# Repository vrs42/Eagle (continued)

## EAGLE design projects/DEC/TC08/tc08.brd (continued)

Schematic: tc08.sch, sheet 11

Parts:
B02, B03, B04, B05: M623; H807
C02, C03: M101; H807

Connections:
76+77: C03.C1 (ENABLE); also elsewhere on the board
!0_TO_AC: B05.H1 (B); also elsewhere on the board
!B-BRK: B02.C1 (C), B02.F2 (C), B02.J1 (C), B02.M2 (C), B02.P1 (C), B02.T2 (C); also elsewhere on the board
!BAC_00: C03.B1 (O1); also elsewhere on the board
!BAC_01: C03.E1 (O2); also elsewhere on the board
!BAC_02: C03.H1 (O3); also elsewhere on the board
!BAC_03: C03.K1 (O4); also elsewhere on the board
!BAC_04: C03.M1 (O5); also elsewhere on the board
!BAC_05: C03.P1 (O6); also elsewhere on the board
!BAC_06: C03.S1 (O7); also elsewhere on the board
!BAC_07: C03.U1 (O8); also elsewhere on the board
!BAC_08: C03.F2 (O9); also elsewhere on the board
!BAC_09: C03.J2 (O10); also elsewhere on the board
!BAC_10: C03.L2 (O11); also elsewhere on the board
!BAC_11: C03.N2 (O12); also elsewhere on the board
!BMB_00: C02.B1 (O1); also elsewhere on the board
!BMB_01: C02.E1 (O2); also elsewhere on the board
!BMB_02: C02.H1 (O3); also elsewhere on the board
!BMB_03: C02.K1 (O4); also elsewhere on the board
!BMB_04: C02.M1 (O5); also elsewhere on the board
!BMB_05: C02.P1 (O6); also elsewhere on the board
!BMB_06: C02.S1 (O7); also elsewhere on the board
!BMB_07: C02.U1 (O8); also elsewhere on the board
!BMB_08: C02.F2 (O9); also elsewhere on the board
!BMB_09: C02.J2 (O10); also elsewhere on the board
!BMB_10: C02.L2 (O11); also elsewhere on the board
!BMB_11: C02.N2 (O12); also elsewhere on the board
!DB_00: B02.D1 (D); also elsewhere on the board
!DB_01: B02.E1 (E); also elsewhere on the board
!DB_02: B02.K1 (D); also elsewhere on the board
!DB_03: B02.L1 (E); also elsewhere on the board
!DB_04: B02.R1 (D); also elsewhere on the board
!DB_05: B02.S1 (E); also elsewhere on the board
!DB_06: B02.H2 (D); also elsewhere on the board
!DB_07: B02.J2 (E); also elsewhere on the board
!DB_08: B02.N2 (D); also elsewhere on the board
!DB_09: B02.P2 (E); also elsewhere on the board
!DB_10: B02.U2 (D); also elsewhere on the board
!DB_11: B02.V2 (E); also elsewhere on the board
!DF: B05.A1 (A); also elsewhere on the board
!DTB_00: B02.A1 (A); also elsewhere on the board
!DTB_01: B02.B1 (B); also elsewhere on the board
!DTB_02: B02.F1 (A); also elsewhere on the board
!DTB_03: B02.H1 (B); also elsewhere on the board
!DTB_04: B02.M1 (A); also elsewhere on the board
!DTB_05: B02.N1 (B); also elsewhere on the board
!DTB_06: B02.D2 (A); also elsewhere on the board
!DTB_07: B02.E2 (B); also elsewhere on the board
!DTB_08: B02.K2 (A); also elsewhere on the board
!DTB_09: B02.L2 (B); also elsewhere on the board
!DTB_10: B02.R2 (A); also elsewhere on the board
!DTB_11: B02.S2 (B); also elsewhere on the board
!DTF: B04.L2 (B); also elsewhere on the board
!EA_00: B05.R1 (D); also elsewhere on the board
!EA_01: B05.S1 (E); also elsewhere on the board
!EA_02: B05.H2 (D); also elsewhere on the board
!EF: B04.A1 (A); also elsewhere on the board
!END: B04.F1 (A); also elsewhere on the board
!ENI: B03.L2 (B); also elsewhere on the board
!FR_00: B03.N1 (B); also elsewhere on the board
!FR_01: B03.D2 (A), B05.E2 (B); also elsewhere on the board
!FR_02: B03.E2 (B); also elsewhere on the board
!FR_03: B03.K2 (A); also elsewhere on the board
!IM_00: B03.D1 (D), B04.D1 (D); also elsewhere on the board
!IM_01: B03.E1 (E), B04.E1 (E); also elsewhere on the board
!IM_02: B03.K1 (D), B04.K1 (D); also elsewhere on the board
!IM_03: B03.L1 (E), B04.L1 (E); also elsewhere on the board
!IM_04: B03.R1 (D), B04.R1 (D); also elsewhere on the board
!IM_05: B03.S1 (E), B04.S1 (E); also elsewhere on the board
!IM_06: B03.H2 (D), B04.H2 (D); also elsewhere on the board
!IM_07: B03.J2 (E), B04.J2 (E); also elsewhere on the board
!IM_08: B03.N2 (D), B04.N2 (D); also elsewhere on the board
!IM_09: B03.P2 (E); also elsewhere on the board
!IM_11: B04.P2 (E); also elsewhere on the board
!INT_RQ: B05.B1 (B); also elsewhere on the board
!MF00: B04.D2 (A), B05.M1 (A); also elsewhere on the board
!MF01: B04.E2 (B), B05.N1 (B); also elsewhere on the board
!MF02: B04.K2 (A), B05.D2 (A); also elsewhere on the board
!MKTK: B04.B1 (B); also elsewhere on the board
!MR00: B03.H1 (B); also elsewhere on the board
!MR01: B03.M1 (A); also elsewhere on the board
!PAR: B04.M1 (A); also elsewhere on the board
!RSTA: B03.C1 (C), B03.F2 (C), B03.J1 (C), B03.M2 (C), B03.P1 (C); also elsewhere on the board
!RSTB: B04.C1 (C), B04.F2 (C), B04.J1 (C), B04.M2 (C), B04.P1 (C); also elsewhere on the board
!SEARCH: B05.K2 (A); also elsewhere on the board
!SEL: B04.H1 (B); also elsewhere on the board
!SKP_RQ: B05.F1 (A); also elsewhere on the board
!TIM: B04.N1 (B); also elsewhere on the board
!USR_00: B03.A1 (A); also elsewhere on the board
!USR_01: B03.B1 (B); also elsewhere on the board
!USR_02: B03.F1 (A); also elsewhere on the board
+3V@C08U1: C02.C1 (ENABLE); also elsewhere on the board
ADDR_ACC: C02.V2 (O15); also elsewhere on the board
GND: B02.C2 (GND), B02.T1 (GND), B02.U1 (GND), B02.V1 (GND), B03.C2 (GND), B03.T1 (GND), B03.U1 (GND), B03.V1 (GND), B04.C2 (GND), B04.T1 (GND), B04.U1 (GND), B04.V1 (GND), B05.C1 (C), B05.C2 (GND), B05.F2 (C), B05.J1 (C), B05.M2 (C), B05.P1 (C), B05.T1 (GND), B05.U1 (GND), B05.V1 (GND), C02.C2 (GND), C02.T1 (GND), C03.C2 (GND), C03.T1 (GND); also elsewhere on the board
I/!O_0_TO_AC: B05.L1 (E); also elsewhere on the board
I/!O_1_TO_CA_INH: B05.N2 (D); also elsewhere on the board
I/!O_ADDR_ACC: C02.U2 (IN15); also elsewhere on the board
I/!O_BRK_RQ: B05.D1 (D); also elsewhere on the board
I/!O_INT_RQ: B05.E1 (E); also elsewhere on the board
I/!O_SKP_RQ: B05.K1 (D); also elsewhere on the board
I/O_BAC_00: C03.A1 (IN1); also elsewhere on the board
I/O_BAC_01: C03.D1 (IN2); also elsewhere on the board
I/O_BAC_02: C03.F1 (IN3); also elsewhere on the board
I/O_BAC_03: C03.J1 (IN4); also elsewhere on the board
I/O_BAC_04: C03.L1 (IN5); also elsewhere on the board
I/O_BAC_05: C03.N1 (IN6); also elsewhere on the board
I/O_BAC_06: C03.R1 (IN7); also elsewhere on the board
I/O_BAC_07: C03.V1 (IN8); also elsewhere on the board
I/O_BAC_08: C03.E2 (IN9); also elsewhere on the board
I/O_BAC_09: C03.H2 (IN10); also elsewhere on the board
I/O_BAC_10: C03.K2 (IN11); also elsewhere on the board
I/O_BAC_11: C03.M2 (IN12); also elsewhere on the board
I/O_BMB_00: C02.A1 (IN1); also elsewhere on the board
I/O_BMB_01: C02.D1 (IN2); also elsewhere on the board
I/O_BMB_02: C02.F1 (IN3); also elsewhere on the board
I/O_BMB_03: C02.J1 (IN4); also elsewhere on the board
I/O_BMB_04: C02.L1 (IN5); also elsewhere on the board
I/O_BMB_05: C02.N1 (IN6); also elsewhere on the board
I/O_BMB_06: C02.R1 (IN7); also elsewhere on the board
I/O_BMB_07: C02.V1 (IN8); also elsewhere on the board
I/O_BMB_08: C02.E2 (IN9); also elsewhere on the board
I/O_BMB_09: C02.H2 (IN10); also elsewhere on the board
I/O_BMB_10: C02.K2 (IN11); also elsewhere on the board
I/O_BMB_11: C02.M2 (IN12); also elsewhere on the board
I/O_DATA_IN: B05.J2 (E); also elsewhere on the board
VCC: B02.A2 (VCC), B03.A2 (VCC), B04.A2 (VCC), B05.A2 (VCC), C02.A2 (VCC), C03.A2 (VCC); also elsewhere on the board

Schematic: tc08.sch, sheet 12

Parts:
A02, A03, A04, A05, A06: M903; H807
A13, A17, A27, A28: H807
A24: W023; H807
A25, A26: M916; H807
B17, B24, B25, B26, B27, B28: H807
C19, C20, C21, C22, C23, C24, C25, C26, C27, C28: H807
D01, D19, D20, D21, D22, D23, D24, D25, D26, D27, D28: H807
D02, D03, D04, D05, D06: M903; H807

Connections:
!DB_00: A06.B1, D06.B1; also elsewhere on the board
!DB_01: A06.D1, D06.D1; also elsewhere on the board
!DB_02: A06.E1, D06.E1; also elsewhere on the board
!DB_03: A06.H1, D06.H1; also elsewhere on the board
!DB_04: A06.J1, D06.J1; also elsewhere on the board
!DB_05: A06.L1, D06.L1; also elsewhere on the board
!DB_06: A06.M1, D06.M1; also elsewhere on the board
!DB_07: A06.P1, D06.P1; also elsewhere on the board
!DB_08: A06.S1, D06.S1; also elsewhere on the board
!DB_09: A06.D2, D06.D2; also elsewhere on the board
!DB_10: A06.E2, D06.E2; also elsewhere on the board
!DB_11: A06.H2, D06.H2; also elsewhere on the board
!EA_00: A06.V2, D06.V2; also elsewhere on the board
!EA_01: A06.T2, D06.T2; also elsewhere on the board
!EA_02: A06.S2, D06.S2; also elsewhere on the board
!IM_00: A04.B1, D04.B1; also elsewhere on the board
!IM_01: A04.D1, D04.D1; also elsewhere on the board
!IM_02: A04.E1, D04.E1; also elsewhere on the board
!IM_03: A04.H1, D04.H1; also elsewhere on the board
!IM_04: A04.J1, D04.J1; also elsewhere on the board
!IM_05: A04.L1, D04.L1; also elsewhere on the board
!IM_06: A04.M1, D04.M1; also elsewhere on the board
!IM_07: A04.P1, D04.P1; also elsewhere on the board
!IM_08: A04.S1, D04.S1; also elsewhere on the board
!IM_09: A04.D2, D04.D2; also elsewhere on the board
!IM_10: A04.E2, D04.E2
!IM_11: A04.H2, D04.H2; also elsewhere on the board
!T_00: A24.V2; also elsewhere on the board
!T_01: A24.M2; also elsewhere on the board
!T_02: A24.N2; also elsewhere on the board
!T_03: A24.P2; also elsewhere on the board
!T_04: A24.R2; also elsewhere on the board
!T_05: A24.S2; also elsewhere on the board
!T_06: A24.T2; also elsewhere on the board
!T_07: A24.U2; also elsewhere on the board
!T_FWD: A24.E2; also elsewhere on the board
!T_GO: A24.C2; also elsewhere on the board
!T_PWR_CLR: A24.H2; also elsewhere on the board
!T_REV: A24.F2; also elsewhere on the board
!T_SINGLE_UNIT: A24.K2; also elsewhere on the board
!T_STOP: A24.D2; also elsewhere on the board
!T_WRITE_OK: A24.L2; also elsewhere on the board
C00: A26.E2; also elsewhere on the board
C01: A26.F2; also elsewhere on the board
DATA: A26.M1; also elsewhere on the board
DF: A26.E1; also elsewhere on the board
DTB_00: A25.A2; also elsewhere on the board
DTB_01: A25.B2; also elsewhere on the board
DTB_02: A25.C2; also elsewhere on the board
DTB_03: A25.D2; also elsewhere on the board
DTB_04: A25.E2; also elsewhere on the board
DTB_05: A25.F2; also elsewhere on the board
DTB_06: A25.H2; also elsewhere on the board
DTB_07: A25.J2; also elsewhere on the board
DTB_08: A25.K2; also elsewhere on the board
DTB_09: A25.L2; also elsewhere on the board
DTB_10: A25.M2; also elsewhere on the board
DTB_11: A25.N2; also elsewhere on the board
DTF: A26.C1; also elsewhere on the board
EF: A25.N1; also elsewhere on the board
END: A25.R1; also elsewhere on the board
ENI: A25.L1; also elsewhere on the board
FR_00: A25.F1; also elsewhere on the board
FR_01: A25.H1; also elsewhere on the board
FR_02: A25.J1; also elsewhere on the board
FR_03: A25.K1; also elsewhere on the board
GND: A02.A1 (GND), A02.C1 (GND), A02.C2 (GND), A02.F1 (GND), A02.F2 (GND), A02.J2 (GND), A02.K1 (GND), A02.L2 (GND), A02.N1 (GND), A02.N2 (GND), A02.R1 (GND), A02.R2 (GND), A02.T1 (GND), A02.U2 (GND), A03.A1 (GND), A03.C1 (GND), A03.C2 (GND), A03.F1 (GND), A03.F2 (GND), A03.J2 (GND), A03.K1 (GND), A03.L2 (GND), A03.N1 (GND), A03.N2 (GND), A03.R1 (GND), A03.R2 (GND), A03.T1 (GND), A03.U2 (GND), A04.A1 (GND), A04.C1 (GND), A04.C2 (GND), A04.F1 (GND), A04.F2 (GND), A04.J2 (GND), A04.K1 (GND), A04.L2 (GND), A04.N1 (GND), A04.N2 (GND), A04.R1 (GND), A04.R2 (GND), A04.T1 (GND), A04.U2 (GND), A05.A1 (GND), A05.B1, A05.C1 (GND), A05.C2 (GND), A05.D1, A05.D2, A05.E1, A05.F1 (GND), A05.F2 (GND), A05.H1, A05.J1, A05.J2 (GND), A05.K1 (GND), A05.L1, A05.L2 (GND), A05.M1, A05.N1 (GND), A05.N2 (GND), A05.P1, A05.R1 (GND), A05.R2 (GND), A05.S1, A05.T1 (GND), A05.U2 (GND), A06.A1 (GND), A06.C1 (GND), A06.C2 (GND), A06.F1 (GND), A06.F2 (GND), A06.J2 (GND), A06.K1 (GND), A06.K2, A06.L2 (GND), A06.N1 (GND), A06.N2 (GND), A06.R1 (GND), A06.R2 (GND), A06.T1 (GND), A06.U2 (GND), A25.M1, A26.D2, A26.U2, A26.V1, D02.A1 (GND), D02.C1 (GND), D02.C2 (GND), D02.F1 (GND), D02.F2 (GND), D02.J2 (GND), D02.K1 (GND), D02.L2 (GND), D02.N1 (GND), D02.N2 (GND), D02.R1 (GND), D02.R2 (GND), D02.T1 (GND), D02.U2 (GND), D03.A1 (GND), D03.C1 (GND), D03.C2 (GND), D03.F1 (GND), D03.F2 (GND), D03.J2 (GND), D03.K1 (GND), D03.L2 (GND), D03.N1 (GND), D03.N2 (GND), D03.R1 (GND), D03.R2 (GND), D03.T1 (GND), D03.U2 (GND), D04.A1 (GND), D04.C1 (GND), D04.C2 (GND), D04.F1 (GND), D04.F2 (GND), D04.J2 (GND), D04.K1 (GND), D04.L2 (GND), D04.N1 (GND), D04.N2 (GND), D04.R1 (GND), D04.R2 (GND), D04.T1 (GND), D04.U2 (GND), D05.A1 (GND), D05.B1, D05.C1 (GND), D05.C2 (GND), D05.D1, D05.D2, D05.E1, D05.F1 (GND), D05.F2 (GND), D05.H1, D05.J1, D05.J2 (GND), D05.K1 (GND), D05.L1, D05.L2 (GND), D05.M1, D05.N1 (GND), D05.N2 (GND), D05.P1, D05.R1 (GND), D05.R2 (GND), D05.S1, D05.T1 (GND), D05.U2 (GND), D06.A1 (GND), D06.C1 (GND), D06.C2 (GND), D06.F1 (GND), D06.F2 (GND), D06.J2 (GND), D06.K1 (GND), D06.K2, D06.L2 (GND), D06.N1 (GND), D06.N2 (GND), D06.R1 (GND), D06.R2 (GND), D06.T1 (GND), D06.U2 (GND); also elsewhere on the board
I/!O_0_TO_AC: A04.P2, D04.P2; also elsewhere on the board
I/!O_1_TO_CA_INH: A06.M2, D06.M2; also elsewhere on the board
I/!O_ADDR_ACC: A05.S2, D05.S2; also elsewhere on the board
I/!O_BMB_03: A03.H1, D03.H1
I/!O_BMB_04: A03.L1, D03.L1
I/!O_BMB_05: A03.P1, D03.P1
I/!O_BMB_06: A03.D2, D03.D2
I/!O_BMB_07: A03.H2, D03.H2
I/!O_BMB_08: A03.M2, D03.M2; also elsewhere on the board
I/!O_BRK_RQ: A05.K2, D05.K2; also elsewhere on the board
I/!O_BWC0: A06.P2, D06.P2; also elsewhere on the board
I/!O_INT_RQ: A04.M2, D04.M2; also elsewhere on the board
I/!O_SKP_RQ: A04.K2, D04.K2; also elsewhere on the board
I/O_B-BRK: A05.P2, D05.P2; also elsewhere on the board
I/O_B-RUN: A04.S2, D04.S2; also elsewhere on the board
I/O_BAC_00: A02.B1, D02.B1; also elsewhere on the board
I/O_BAC_01: A02.D1, D02.D1; also elsewhere on the board
I/O_BAC_02: A02.E1, D02.E1; also elsewhere on the board
I/O_BAC_03: A02.H1, D02.H1; also elsewhere on the board
I/O_BAC_04: A02.J1, D02.J1; also elsewhere on the board
I/O_BAC_05: A02.L1, D02.L1; also elsewhere on the board
I/O_BAC_06: A02.M1, D02.M1; also elsewhere on the board
I/O_BAC_07: A02.P1, D02.P1; also elsewhere on the board
I/O_BAC_08: A02.S1, D02.S1; also elsewhere on the board
I/O_BAC_09: A02.D2, D02.D2; also elsewhere on the board
I/O_BAC_10: A02.E2, D02.E2; also elsewhere on the board
I/O_BAC_11: A02.H2, D02.H2; also elsewhere on the board
I/O_BMB_00: A03.B1, D03.B1; also elsewhere on the board
I/O_BMB_01: A03.D1, D03.D1; also elsewhere on the board
I/O_BMB_02: A03.E1, D03.E1; also elsewhere on the board
I/O_BMB_03: A03.J1, D03.J1; also elsewhere on the board
I/O_BMB_04: A03.M1, D03.M1; also elsewhere on the board
I/O_BMB_05: A03.S1, D03.S1; also elsewhere on the board
I/O_BMB_06: A03.E2, D03.E2; also elsewhere on the board
I/O_BMB_07: A03.K2, D03.K2; also elsewhere on the board
I/O_BMB_08: A03.P2, D03.P2; also elsewhere on the board
I/O_BMB_09: A03.S2, D03.S2; also elsewhere on the board
I/O_BMB_10: A03.T2, D03.T2; also elsewhere on the board
I/O_BMB_11: A03.V2, D03.V2; also elsewhere on the board
I/O_DATA_IN: A05.M2, D05.M2; also elsewhere on the board
I/O_PWR_CLR: A02.V2, D02.V2; also elsewhere on the board
I/O_TS03: A02.S2, D02.S2; also elsewhere on the board
I/O_TS04: A02.T2, D02.T2
IOP_1: A02.K2, D02.K2; also elsewhere on the board
IOP_2: A02.M2, D02.M2; also elsewhere on the board
IOP_4: A02.P2, D02.P2; also elsewhere on the board
LPB_00: A25.T2; also elsewhere on the board
LPB_01: A25.U2; also elsewhere on the board
LPB_02: A25.V2; also elsewhere on the board
LPB_03: A26.A2; also elsewhere on the board
LPB_04: A26.B2; also elsewhere on the board
LPB_05: A26.C2; also elsewhere on the board
MC00: A26.S1; also elsewhere on the board
MC01: A26.T1; also elsewhere on the board
MC02: A26.U1; also elsewhere on the board
MF00: A25.V1; also elsewhere on the board
MF01: A26.A1; also elsewhere on the board
MF02: A26.B1; also elsewhere on the board
MKT: A26.H2; also elsewhere on the board
MKTK: A25.P1; also elsewhere on the board
MR00: A25.D1; also elsewhere on the board
MR01: A25.E1; also elsewhere on the board
PAR: A25.T1; also elsewhere on the board
SEL: A25.S1; also elsewhere on the board
ST_BLK_MK: A26.K1; also elsewhere on the board
ST_CK: A26.P1; also elsewhere on the board
ST_FINAL: A26.N1; also elsewhere on the board
ST_IDLE: A26.R1; also elsewhere on the board
ST_REV_CK: A26.L1; also elsewhere on the board
SWTM: A26.V2; also elsewhere on the board
TIM: A25.U1; also elsewhere on the board
USR_00: A25.A1; also elsewhere on the board
USR_01: A25.B1; also elsewhere on the board
USR_02: A25.C1; also elsewhere on the board
UTS: A26.J1; also elsewhere on the board
W01: A26.J2; also elsewhere on the board
W02: A26.K2; also elsewhere on the board
W03: A26.L2; also elsewhere on the board
W04: A26.M2; also elsewhere on the board
W05: A26.N2; also elsewhere on the board
W06: A26.P2; also elsewhere on the board
W07: A26.R2; also elsewhere on the board
W08: A26.S2; also elsewhere on the board
W09: A26.T2; also elsewhere on the board
WB00: A25.P2; also elsewhere on the board
WB01: A25.R2; also elsewhere on the board
WB02: A25.S2; also elsewhere on the board
WC: A26.H1; also elsewhere on the board
WR_EN: A26.F1; also elsewhere on the board

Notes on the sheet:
Empty Slots:

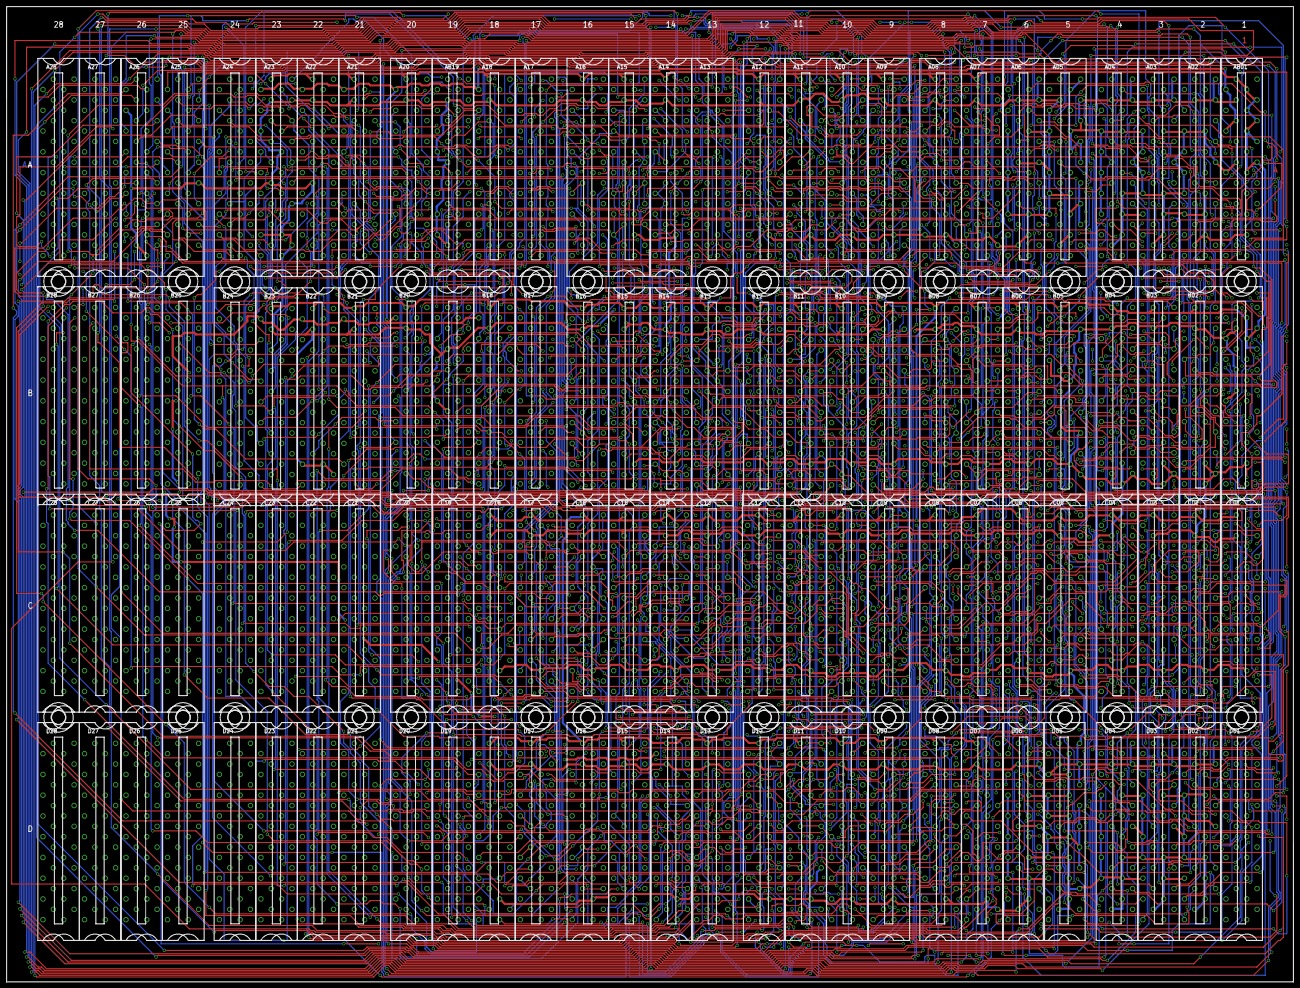
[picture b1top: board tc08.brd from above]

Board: 4 copper layers, 393.8 x 298.4 mm, 137 parts (0 on the bottom side), 538 nets.

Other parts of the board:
U$17, U$18, U$19, U$20, U$66, U$67, U$68, U$69, U$70, U$71, U$72, U$73, U$74, U$75, U$76, U$77, U$78, U$79, U$80, U$81, U$82, U$83, U$84, U$85, U$86, U$87, U$88, U$90: 4,3

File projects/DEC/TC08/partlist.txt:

Partlist

Exported from tc08.sch at  8/08/2006 10:36:56a

EAGLE Version 4.11 Copyright (c) 1988-2003 CadSoft

Part     Value          Device     Package  Library  Sheet

A02      M903           M903       H807     dec-m    12
A03      M903           M903       H807     dec-m    12
A04      M903           M903       H807     dec-m    12
A05      M903           M903       H807     dec-m    12
A06      M903           M903       H807     dec-m    12
A07      M161           M161       H807     dec-m    2
A08      M206           M206X      H807     dec-m    4
A09      M117           M117       H807     dec-m    2
A10      M113           M113       H807     dec-m    2
A11      M111           M111       H807     dec-m    1
A12      M113           M113       H807     dec-m    1
A14      M302           M302       H807     dec-m    3
A15      M627           M627       H807     dec-m    3
A16      M602           M602       H807     dec-m    3
A18      G888           G888       H807     dec-m    10
A20      G888           G888       H807     dec-m    10
A21      G888           G888       H807     dec-m    10
A22      M502           M502       H807     dec-m    2
A23      M633           M633       H807     dec-m    2
A24      W023           W023       H807     dec-m    12
A25      M916           M916       H807     dec-m    12
A26      M916           M916       H807     dec-m    12
AB01     G821           G821       H807-2   dec-m    10
AB19     W032           W032       H807-2   dec-m    10
B02      M623           M623       H807     dec-m    11
B03      M623           M623       H807     dec-m    11
B04      M623           M623       H807     dec-m    11
B05      M623           M623       H807     dec-m    11
B06      M111           M111       H807     dec-m    1
B07      M207           M207       H807     dec-m    2
B08      M113           M113       H807     dec-m    1
B09      M206           M206X      H807     dec-m    8
B10      M627           M627       H807     dec-m    1
B11      M115           M115       H807     dec-m    2
B12      M117           M117       H807     dec-m    4
B13      M206           M206X      H807     dec-m    4
B14      M206           M206X      H807     dec-m    2
B15      M113           M113       H807     dec-m    3
B16      M602           M602       H807     dec-m    3
B18      G888           G888       H807     dec-m    10
B20      G888           G888       H807     dec-m    10
B21      G879           G879       H807     dec-m    6
B22      M633           M633       H807     dec-m    2
B23      W005           W005       H807     dec-m    2
C01      M101           M101       H807     dec-m    1
C02      M101           M101-ARRAY H807     dec-m    11
C03      M101           M101-ARRAY H807     dec-m    11
C04      M103           M103       H807     dec-m    1
C05      M103           M103       H807     dec-m    1
C06      M111           M111       H807     dec-m    1
C07      M207           M207       H807     dec-m    2
C08      M121           M121       H807     dec-m    1
C09      M206           M206X      H807     dec-m    8
C10      M121           M121       H807     dec-m    6
C11      M113           M113       H807     dec-m    4
C12      M115           M115       H807     dec-m    3
C13      M111           M111       H807     dec-m    3
C14      M206           M206X      H807     dec-m    3
C15      M113           M113       H807     dec-m    3
C16      M627           M627       H807     dec-m    1
C17      M111           M111       H807     dec-m    1
CD18     M228           M228       H807-2   dec-m    7
D02      M903           M903       H807     dec-m    12
D03      M903           M903       H807     dec-m    12
D04      M903           M903       H807     dec-m    12
D05      M903           M903       H807     dec-m    12
D06      M903           M903       H807     dec-m    12
D07      M161           M161       H807     dec-m    2
D08      M207           M207       H807     dec-m    9
D09      M121           M121       H807     dec-m    2
D10      M119           M119       H807     dec-m    3
D11      M206           M206X      H807     dec-m    1
D12      M627           M627       H807     dec-m    1
D13      M602           M602       H807     dec-m    1
D14      M307           M307       H807     dec-m    3
D15      M401           M401       H807     dec-m    3
D16      M302           M302       H807     dec-m    6
D17      M602           M602       H807     dec-m    1

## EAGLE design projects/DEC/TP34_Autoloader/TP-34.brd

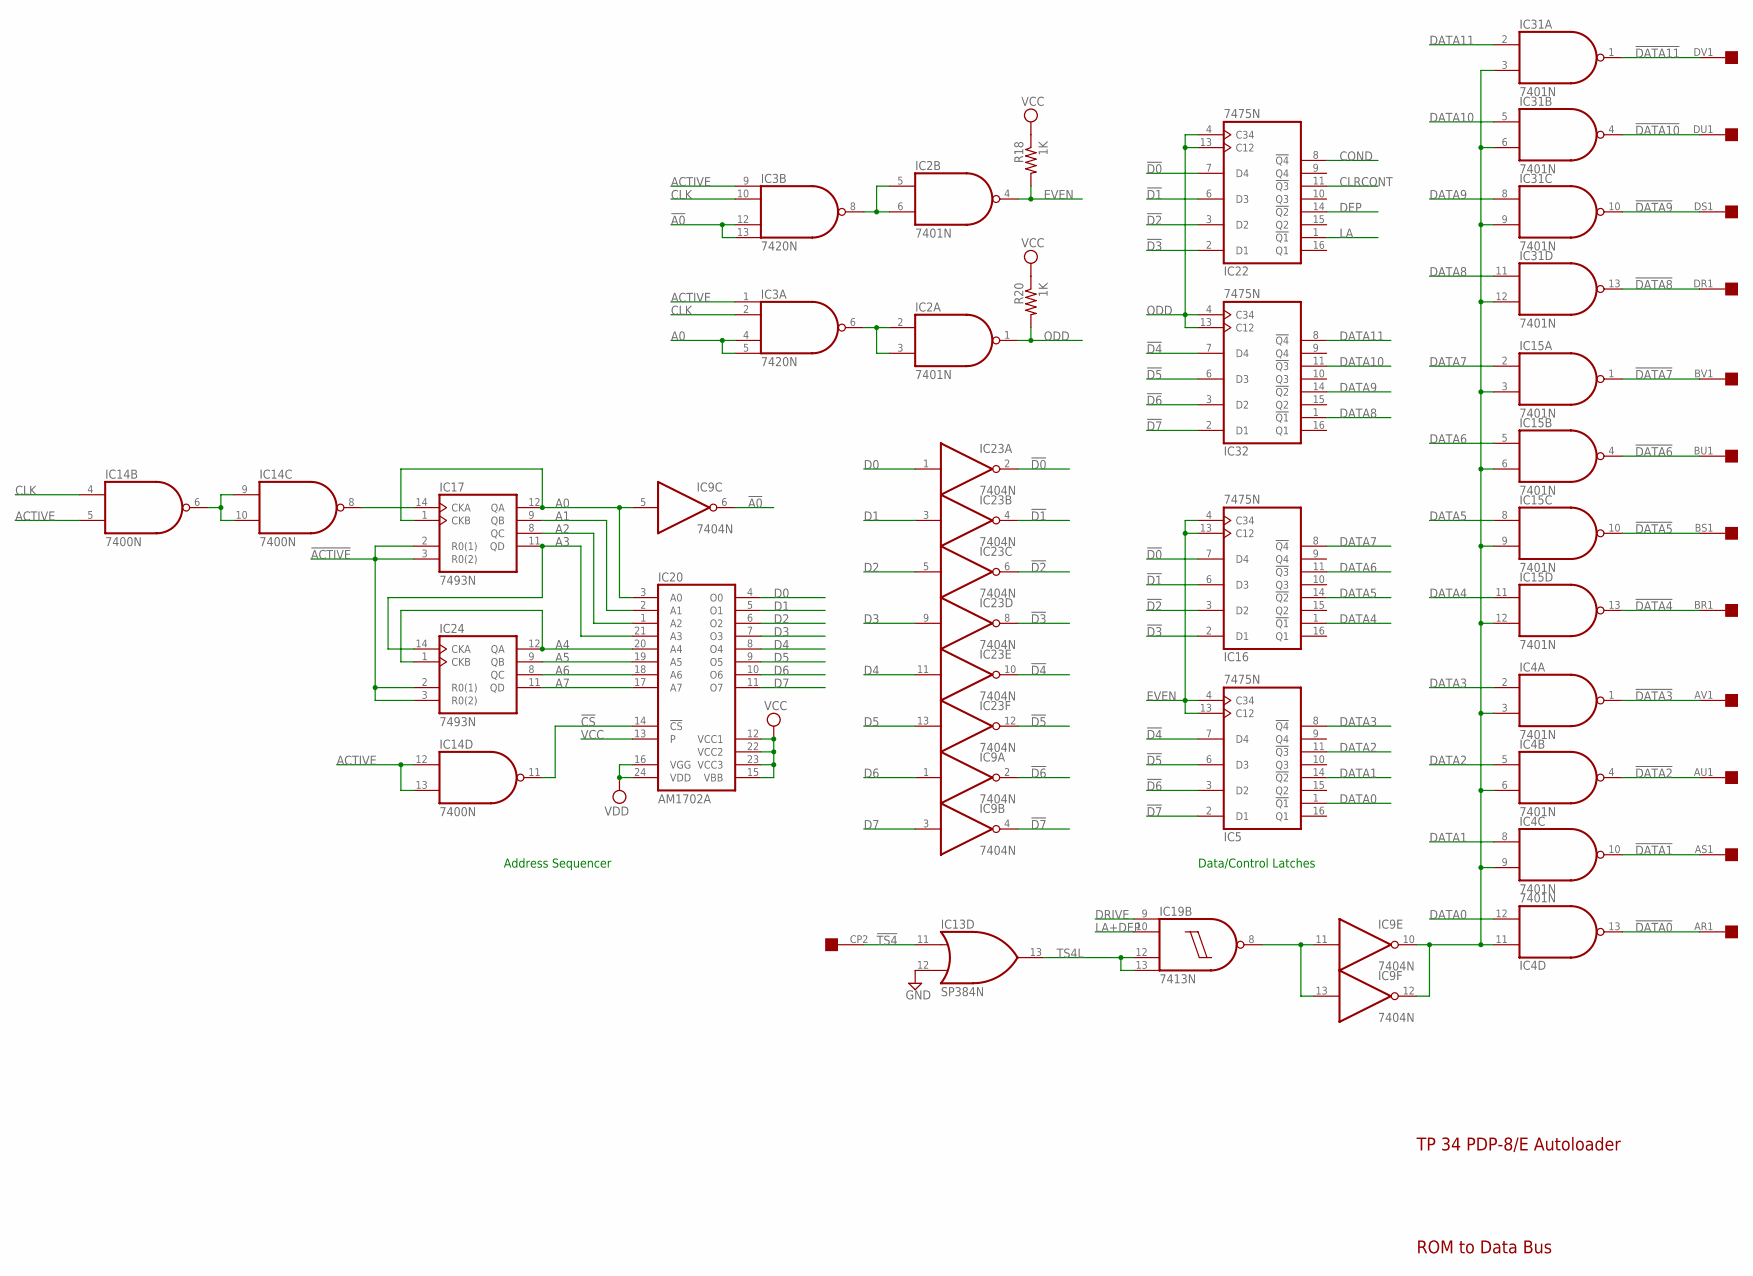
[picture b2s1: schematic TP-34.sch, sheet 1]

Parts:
IC2, IC4, IC15, IC31: 7401N; DIL14
IC3: 7420N; DIL14
IC5, IC16, IC22, IC32: 7475N; DIL16
IC9, IC23: 7404N; DIL14
IC13: SP384N; DIL14
IC14: 7400N; DIL14
IC17, IC24: 7493N; DIL14
IC19: 7413N; DIL14
IC20: AM1702A; DIL24
R18, R20: 1K; 0207/10
U$2: QUAD; EDGE-CON8

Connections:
!A0: IC3.12 (I2), IC3.13 (I3), IC9.6 (O)
!ACTIVE: IC17.2 (R0(1)), IC17.3 (R0(2)), IC24.2 (R0(1)), IC24.3 (R0(2)); also elsewhere on the board
!CS: IC14.11 (O), IC20.14 (!CS)
!D0: IC16.7 (D4), IC22.7 (D4), IC23.2 (O)
!D1: IC16.6 (D3), IC22.6 (D3), IC23.4 (O)
!D2: IC16.3 (D2), IC22.3 (D2), IC23.6 (O)
!D3: IC16.2 (D1), IC22.2 (D1), IC23.8 (O)
!D4: IC5.7 (D4), IC23.10 (O), IC32.7 (D4)
!D5: IC5.6 (D3), IC23.12 (O), IC32.6 (D3)
!D6: IC5.3 (D2), IC9.2 (O), IC32.3 (D2)
!D7: IC5.2 (D1), IC9.4 (O), IC32.2 (D1)
!DATA0: IC4.13 (O), U$2.AR1
!DATA1: IC4.10 (O), U$2.AS1
!DATA2: IC4.4 (O), U$2.AU1
!DATA3: IC4.1 (O), U$2.AV1
!DATA4: IC15.13 (O), U$2.BR1
!DATA5: IC15.10 (O), U$2.BS1
!DATA6: IC15.4 (O), U$2.BU1
!DATA7: IC15.1 (O), U$2.BV1
!DATA8: IC31.13 (O), U$2.DR1
!DATA9: IC31.10 (O), U$2.DS1
!DATA10: IC31.4 (O), U$2.DU1
!DATA11: IC31.1 (O), U$2.DV1
!TS4: IC13.11 (I0), U$2.CP2
A0: IC3.4 (I2), IC3.5 (I3), IC9.5 (I), IC17.1 (CKB), IC17.12 (QA), IC20.3 (A0)
A1: IC17.9 (QB), IC20.2 (A1)
A2: IC17.8 (QC), IC20.1 (A2)
A3: IC17.11 (QD), IC20.21 (A3), IC24.14 (CKA)
A4: IC20.20 (A4), IC24.1 (CKB), IC24.12 (QA)
A5: IC20.19 (A5), IC24.9 (QB)
A6: IC20.18 (A6), IC24.8 (QC)
A7: IC20.17 (A7), IC24.11 (QD)
ACTIVE: IC3.1 (I0), IC3.9 (I0), IC14.5 (I1), IC14.12 (I0), IC14.13 (I1); also elsewhere on the board
CLK: IC3.2 (I1), IC3.10 (I1), IC14.4 (I0); also elsewhere on the board
CLRCONT: IC22.11 (!Q3); also elsewhere on the board
COND: IC22.8 (!Q4); also elsewhere on the board
D0: IC20.4 (O0), IC23.1 (I)
D1: IC20.5 (O1), IC23.3 (I)
D2: IC20.6 (O2), IC23.5 (I)
D3: IC20.7 (O3), IC23.9 (I)
D4: IC20.8 (O4), IC23.11 (I)
D5: IC20.9 (O5), IC23.13 (I)
D6: IC9.1 (I), IC20.10 (O6)
D7: IC9.3 (I), IC20.11 (O7)
DATA0: IC4.12 (I1), IC5.1 (!Q1)
DATA1: IC4.8 (I0), IC5.14 (!Q2)
DATA2: IC4.5 (I0), IC5.11 (!Q3)
DATA3: IC4.2 (I0), IC5.8 (!Q4)
DATA4: IC15.11 (I0), IC16.1 (!Q1)
DATA5: IC15.8 (I0), IC16.14 (!Q2)
DATA6: IC15.5 (I0), IC16.11 (!Q3)
DATA7: IC15.2 (I0), IC16.8 (!Q4)
DATA8: IC31.11 (I0), IC32.1 (!Q1)
DATA9: IC31.8 (I0), IC32.14 (!Q2)
DATA10: IC31.5 (I0), IC32.11 (!Q3)
DATA11: IC31.2 (I0), IC32.8 (!Q4)
DEP: IC22.14 (!Q2); also elsewhere on the board
DRIVE: IC19.9 (I0); also elsewhere on the board
EVEN: IC2.4 (O), IC5.4 (C34), IC5.13 (C12), IC16.4 (C34), IC16.13 (C12), R18.2
GND: IC2.7 (GND), IC3.7 (GND), IC4.7 (GND), IC5.12 (GND), IC9.7 (GND), IC13.1 (GND), IC13.12 (I1), IC14.7 (GND), IC15.7 (GND), IC16.12 (GND), IC17.10 (GND), IC19.7 (GND), IC22.12 (GND), IC23.7 (GND), IC24.10 (GND), IC31.7 (GND), IC32.12 (GND); also elsewhere on the board
LA: IC22.1 (!Q1); also elsewhere on the board
LA+DEP: IC19.10 (I1); also elsewhere on the board
unnamed: IC2.2 (I0), IC2.3 (I1), IC3.6 (O)
unnamed: IC2.5 (I0), IC2.6 (I1), IC3.8 (O)
unnamed: IC4.3 (I1), IC4.6 (I1), IC4.9 (I1), IC4.11 (I0), IC9.10 (O), IC9.12 (O), IC15.3 (I1), IC15.6 (I1), IC15.9 (I1), IC15.12 (I1), IC31.3 (I1), IC31.6 (I1), IC31.9 (I1), IC31.12 (I1)
unnamed: IC9.11 (I), IC9.13 (I), IC19.8 (O)
unnamed: IC14.6 (O), IC14.9 (I0), IC14.10 (I1)
unnamed: IC14.8 (O), IC17.14 (CKA)
ODD: IC2.1 (O), IC22.4 (C34), IC22.13 (C12), IC32.4 (C34), IC32.13 (C12), R20.2; also elsewhere on the board
TS4L: IC13.13 (O), IC19.12 (I2), IC19.13 (I3)
VCC: IC2.14 (VCC), IC3.14 (VCC), IC4.14 (VCC), IC5.5 (VCC), IC9.14 (VCC), IC13.8 (VCC), IC14.14 (VCC), IC15.14 (VCC), IC16.5 (VCC), IC17.5 (VCC), IC19.14 (VCC), IC20.12 (VCC1), IC20.13, IC20.15 (VBB), IC20.22 (VCC2), IC20.23 (VCC3), IC22.5 (VCC), IC23.14 (VCC), IC24.5 (VCC), IC31.14 (VCC), IC32.5 (VCC), R18.1, R20.1; also elsewhere on the board
VDD: IC20.16 (VGG), IC20.24 (VDD); also elsewhere on the board

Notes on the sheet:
TP 34 PDP-8/E Autoloader
ROM to Data Bus
Address Sequencer
Data/Control Latches
